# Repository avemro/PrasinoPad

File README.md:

# PrasinoPad
###### $${\color{gray}\text{Prasino: Prasinos = Green (from greek language)}}$$

Customizable 4-key macropad with the Seeed Studio XIAO RP2040 microcontroller along with Cherry MX switches, an EC11 rotary encoder, and a 0.91" I2C OLED display, which is controlled by QMK firmware.

Depending on whether one needs a media controller, scrubbing for video editing, or simply some hotkeys for application control, PrasinoPad provides the possibility to have everything at hands without unnecessary desk cluttering.

---

## Features

* **Direct-Pin Switching**: As there are only 4 keys, each switch is connected directly to the GPIO pin of the MCU pulled to the ground, eliminating the need for any diode matrix.
* **Rotation Knob**: Alps/EC11 rotary encoder for controlling volume, scrolling, or scrubbing along the timeline, featuring a built-in tactile switch.
* **Status Indicators**: 0.91" 128x32 OLED display over I2C to display active layers, volume level, or status icons.
* **Sleek Microcontroller**: Equipped with the Seeed Studio XIAO RP2040, mounted directly on the underside of the board to keep the desk footprint small.
* **Personalized Shell**: 3D-printed body with special slots for the switch plate, knob, and OLED display.

---

## Hardware Gallery

### Assembled Render

### 3D Printed Enclosure

### KiCad Schematic

### PCB Layout

---

## Pinout & Wiring

The XIAO RP2040 is soldered to the bottom layer (`B.Cu`) with direct access to all the board components:

| Component | Function | XIAO Pin (KiCad Net) | RP2040 GPIO | Description |
| :--- | :--- | :--- | :--- | :--- |
| **SW1** | Key 1 | `D0` (`PA02_A0_D0`) | GP26 | Pulled low to GND on press |
| **SW2** | Key 2 | `D1` (`PA4_A1_D1`) | GP27 | Pulled low to GND on press |
| **SW3** | Key 3 | `D2` (`PA10_A2_D2`) | GP28 | Pulled low to GND on press |
| **SW4** | Key 4 | `D3` (`PA11_A3_D3`) | GP29 | Pulled low to GND on press |
| **SW5 (Enc)** | Channel A | `D8` (`PA7_A8_D8_SCK`) | GP4 | Encoder quadrature signal A |
| **SW5 (Enc)** | Channel B | `D9` (`PA5_A9_D9_MISO`) | GP3 | Encoder quadrature signal B |
| **SW5 (Switch)**| Encoder Push| `D7` (`PB09_A7_D7_RX`) | GP1 | Pulled low to GND on click |
| **OLED (J1 Pin 4)**| I2C SDA | `D4` (`PA8_A4_D4_SDA`) | GP6 | Serial Data line |
| **OLED (J1 Pin 3)**| I2C SCL | `D5` (`PA9_A5_D5_SCL`) | GP7 | Serial Clock line |
| **OLED (J1 Pin 2)**| Power | `3V3` | 3.3V Rail | Logic power |
| **OLED (J1 Pin 1)**| Ground | `GND` | Ground | Common system ground |

---

## Bill of Materials (BOM)

| Item | Qty | Details | Footprint / Notes |
| :--- | :--- | :--- | :--- |
| **Seeed Studio XIAO RP2040** | 1 | RP2040 microcontroller development board | Hybrid SMD / THT footprint on PCB rear |
| **Cherry MX Switches** | 4 | Standard mechanical keyswitches | 1.00u PCB mount footprint |
| **1U Keycaps** | 4 | Standard profile keycaps (OEM / Cherry / XDA) | Fits standard MX stem |
| **EC11 Rotary Encoder** | 1 | Incremental encoder with tactile push switch | Alps EC12E vertical footprint |
| **0.91" OLED Display** | 1 | 128x32 monochrome I2C display | 4-pin interface |
| **Female Pin Header** | 1 | 1x4 2.54mm pitch female header | Socket for the OLED screen |
| **3D Printed Case & Plate** | 1 | Printed housing (PLA or PETG) | Case STL files |
| **Hardware** | 4 | M2 or M3 screws | Secures the plate to the case |

---

## Firmware Configuration

PrasinoPad employs Direct-pin mapping in QMK:

1. **Matrix Mapping**: In your keyboard configuration file, add `DIRECT_PINS` pin mappings for switches with `GP26`, `GP27`, `GP28`, and `GP29`.
2. **Encoders Configuration**: Add `ENCODERS_PAD_A { GP4 }` and `ENCODERS_PAD_B { GP3 }`. The encoder switch will be mapped as a regular key in the direct matrix (`GP1`).
3. **OLED Display**: Add `OLED_ENABLE = yes` and `OLED_DRIVER = SSD1306` in `rules.mk` and configure I2C pins to `GP7` (SCL), `GP6` (SDA).
4. **Programming**:
    * Press the **BOOT** button on the XIAO RP2040 while connecting the USB-C connector.
    * Mount the board as a mass storage device (`RPI-RP2`) and copy your compiled `.uf2` file into that drive.

---

## Assembly Hints

* **Order of Soldering**: First solder the XIAO RP2040 board to the back of the PCB, then the 4-pin OLED header socket, Cherry MX switches and rotary encoder.
* **OLED Positioning**: With a pin header socket used instead of direct soldering of the display you will be able to adjust its position and make sure that it is level with the window of the case.
* **Printing Parameters**: 0.2mm layer thickness, 3-4 perimeters and 20% fill should give enough stiffness for the switch holes and screw holes.

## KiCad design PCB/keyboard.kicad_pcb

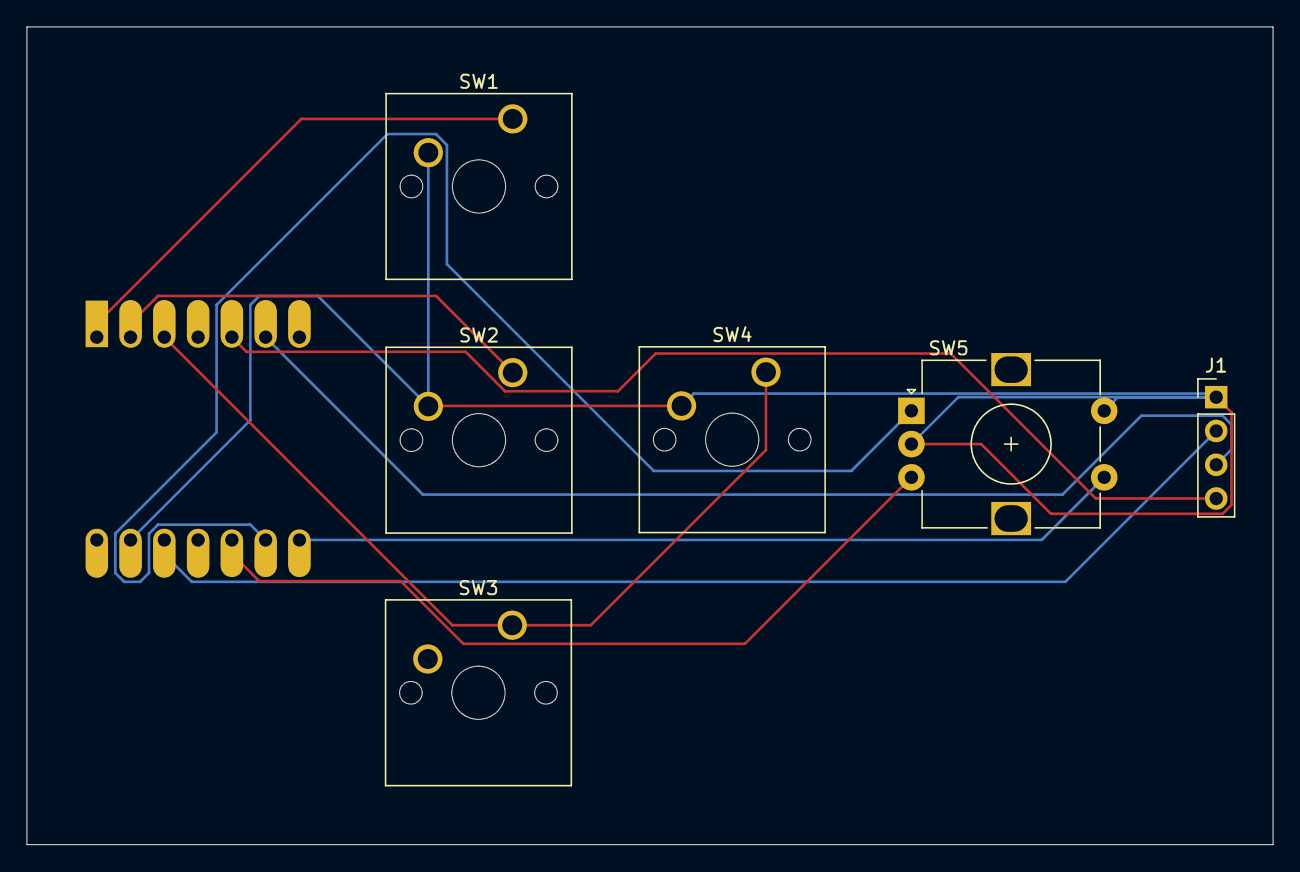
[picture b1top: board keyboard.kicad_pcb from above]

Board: 2 copper layers, 93.7 x 61.5 mm, 7 parts (1 on the bottom side), 10 nets.

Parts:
J1: Conn_01x04_Pin; PinHeader_1x04_P2.54mm_Vertical
SW1, SW2, SW3, SW4: SW_Push; SW_Cherry_MX_1.00u_PCB
SW5: RotaryEncoder_Switch; RotaryEncoder_Alps_EC12E-Switch_Vertical_H20mm
U1: MOUDLE-SEEEDUINO-XIAO; XIAO-Generic-Hybrid-14P-2.54-21X17.8MM

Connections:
GND: J1.1, SW1.2, SW2.2, SW4.2, SW5.C, SW5.S1, U1.13 (GND)
unnamed: J1.2, U1.12 (3V3)
unnamed: J1.3, U1.6 (PA9_A5_D5_SCL)
unnamed: J1.4, U1.5 (PA8_A4_D4_SDA)
unnamed: SW1.1, U1.1 (PA02_A0_D0)
unnamed: SW2.1, U1.2 (PA4_A1_D1)
unnamed: SW5.B, U1.10 (PA5_A9_D9_MISO)
unnamed: SW5.A, U1.9 (PA7_A8_D8_SCK)
unnamed: SW3.1, SW4.1, U1.3 (PA10_A2_D2)
unnamed: SW5.S2, U1.8 (PB09_A7_D7_RX)
